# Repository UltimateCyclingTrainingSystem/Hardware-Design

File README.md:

# Strain-Gauge

Here is a link on how to setup strain gauge with an arduino: 
https://www.youtube.com/watch?v=YsHftv-RgGE

Site of load cell design:
http://www.nakka-rocketry.net/strainlc.html#Prototype

Strain Gage weight sensor and strain gage introduction:
http://morf.lv/modules.php?name=tutorials&lasit=19

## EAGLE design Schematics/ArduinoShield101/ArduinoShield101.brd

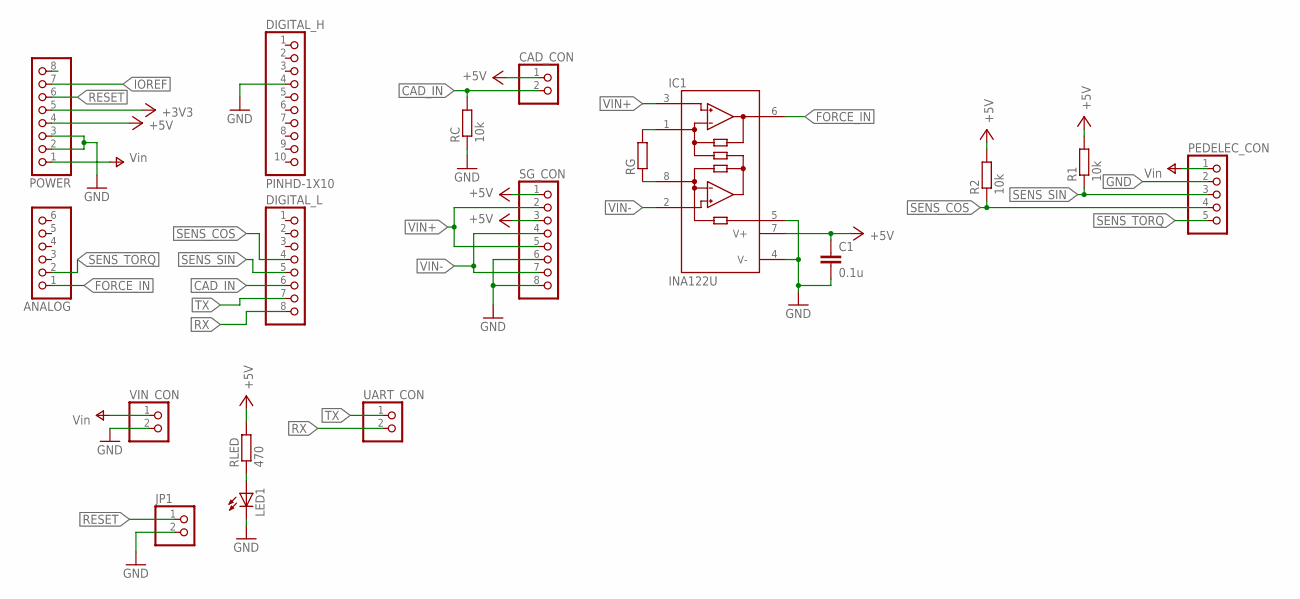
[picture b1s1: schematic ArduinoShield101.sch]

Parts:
ANALOG: PINHD-1X6B; 1X06-BIG
C1: 0.1u; C0603
CAD_CON: PINHD-1X2/90; 1X02/90
DIGITAL_H: PINHD-1X10; 1X10-BIG
DIGITAL_L: PINHD-1X8BIG; 1X08-BIG
IC1: INA122U; SO08
JP1: PINHD-1X2; 1X02
LED1: LEDCHIPLED_0603; CHIPLED_0603
PEDELEC_CON: PINHD-1X5/90; 1X05/90
POWER: PINHD-1X8BIG; 1X08-BIG
R1, R2: 10k; R0603
RC: 10k; R0603
RG: R-EU_R0603; R0603
RLED: 470; R0603
SG_CON: PINHD-1X8/90; 1X08/90
UART_CON: PINHD-1X2/90; 1X02/90
VIN_CON: PINHD-1X2/90; 1X02/90

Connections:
+3V3: POWER.5
+5V: C1.1, CAD_CON.1, IC1.7 (V+), POWER.4, R1.2, R2.2, RLED.2, SG_CON.1, SG_CON.3
CAD_IN: CAD_CON.2, DIGITAL_L.6, RC.2
FORCE_IN: ANALOG.1, IC1.6 (OUT)
GND: C1.2, DIGITAL_H.4, IC1.4 (V-), IC1.5 (REF), JP1.2, LED1.C, PEDELEC_CON.2, POWER.2, POWER.3, RC.1, SG_CON.6, SG_CON.8, VIN_CON.2
IOREF: POWER.7
unnamed: IC1.1 (RG), RG.2
unnamed: IC1.8 (RG), RG.1
unnamed: LED1.A, RLED.1
RESET: JP1.1, POWER.6
RX: DIGITAL_L.8, UART_CON.2
SENS_COS: DIGITAL_L.4, PEDELEC_CON.4, R2.1
SENS_SIN: DIGITAL_L.5, PEDELEC_CON.3, R1.1
SENS_TORQ: ANALOG.2, PEDELEC_CON.5
TX: DIGITAL_L.7, UART_CON.1
V+: PEDELEC_CON.1, POWER.1, VIN_CON.1
VIN+: IC1.3 (+IN), SG_CON.2, SG_CON.5
VIN-: IC1.2 (-IN), SG_CON.4, SG_CON.7

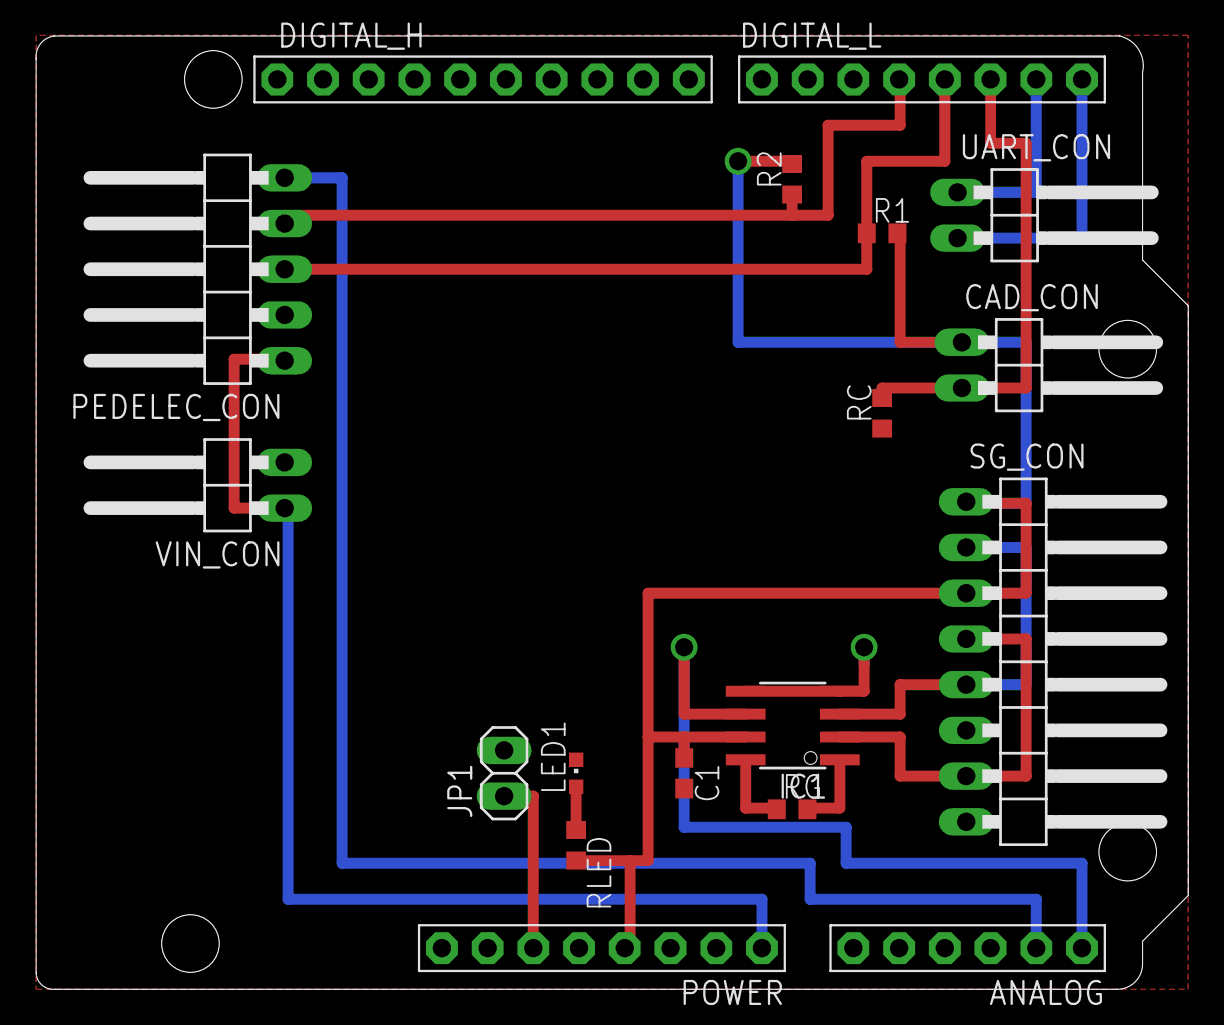
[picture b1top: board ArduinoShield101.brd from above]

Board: 2 copper layers, 64.0 x 53.0 mm, 18 parts (0 on the bottom side), 16 nets.

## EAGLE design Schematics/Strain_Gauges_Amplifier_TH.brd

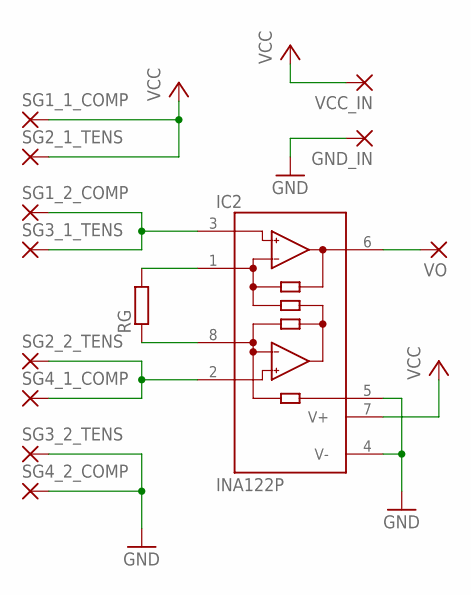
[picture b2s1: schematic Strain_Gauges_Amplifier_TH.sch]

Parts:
GND_IN: SMD2; SMD1,27-2,54
IC2: INA122P; DIL08
RG: R-EU_0204/7; 0204/7
SG1_1_COMP, SG1_2_COMP, SG2_1_TENS, SG2_2_TENS, SG3_1_TENS, SG3_2_TENS, SG4_1_COMP, SG4_2_COMP: SMD2; SMD1,27-2,54
VCC_IN: SMD2; SMD1,27-2,54
VO: SMD2; SMD1,27-2,54

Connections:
GND: GND_IN.1, IC2.4 (V-), IC2.5 (REF), SG3_2_TENS.1, SG4_2_COMP.1
unnamed: IC2.1 (RG), RG.2
unnamed: IC2.8 (RG), RG.1
unnamed: IC2.3 (+IN), SG1_2_COMP.1, SG3_1_TENS.1
unnamed: IC2.2 (-IN), SG2_2_TENS.1, SG4_1_COMP.1
VCC: IC2.7 (V+), SG1_1_COMP.1, SG2_1_TENS.1, VCC_IN.1
VO: IC2.6 (OUT), VO.1

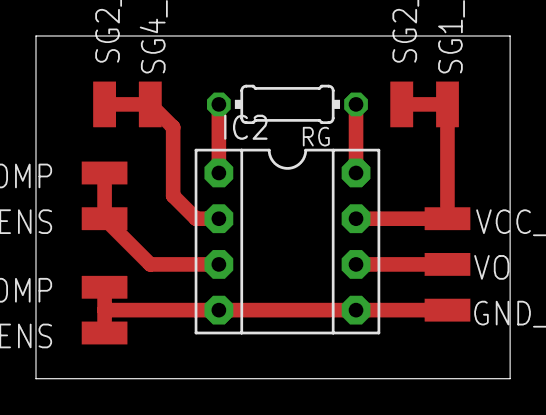
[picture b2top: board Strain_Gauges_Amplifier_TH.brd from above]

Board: 2 copper layers, 26.3 x 19.0 mm, 13 parts (0 on the bottom side), 7 nets.

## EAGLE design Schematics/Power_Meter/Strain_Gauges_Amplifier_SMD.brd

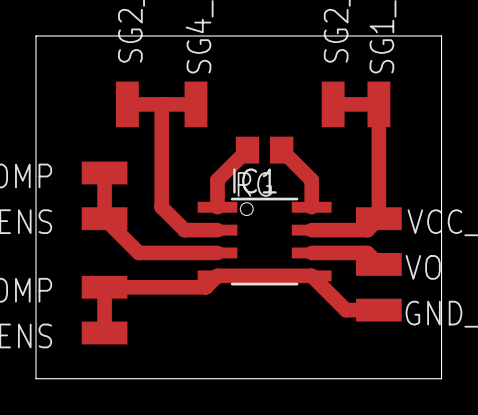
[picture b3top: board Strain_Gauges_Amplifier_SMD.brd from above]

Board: 2 copper layers, 22.5 x 19.0 mm, 13 parts (0 on the bottom side), 7 nets.

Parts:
GND_IN: SMD1,27-2,54
IC1: INA122U; SO08
RG: R0805
SG1_1_COMP, SG1_2_COMP, SG2_1_TENS, SG2_2_TENS, SG3_1_TENS, SG3_2_TENS, SG4_1_COMP, SG4_2_COMP: SMD1,27-2,54
VCC_IN: SMD1,27-2,54
VO: SMD1,27-2,54

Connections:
GND: GND_IN.1, IC1.4, IC1.5, SG3_2_TENS.1, SG4_2_COMP.1
unnamed: IC1.1, RG.2
unnamed: IC1.8, RG.1
unnamed: IC1.3, SG1_2_COMP.1, SG3_1_TENS.1
unnamed: IC1.2, SG2_2_TENS.1, SG4_1_COMP.1
VCC: IC1.7, SG1_1_COMP.1, SG2_1_TENS.1, VCC_IN.1
VO: IC1.6, VO.1

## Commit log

2016-05-11 Add files via upload
    Added reference documents for the power meter design.
2016-06-07 Added EAGLE Schematics and Board
    For both SMD and TH
2016-06-13 Reorganization of files
    Changed the location and names of files.
2016-06-15 Added PCB design.
    Both example WiFi Shield and own Shield.
2016-06-17 Updated Arduino Shield to the version that was printed.
    Includes CAM files.
    Some changes must be made to the Shield to ease mounting/soldering.
2016-06-29 Added strain gages calculations and arduino case examples.
2016-07-04 Added 9V Calibration values and 3d printer manual.
2016-07-24 Added Arduino Box design
2016-07-24 Reorganized files.
